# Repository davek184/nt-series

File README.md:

Changes from original nt-980
* Bottom row alternate layouts
* Stepped caps lock support
* Rotated numpad plus and enter keys
* Added alternate LED location under numlock key
* Added reset pin next to the right spacebar stab (to go into bootloader mode)
* Added second JST connector (JST 2.0 5 pin)
* Labeling on front and back (trying something)

It does work with the stock plate but only for the original layout.  Other layouts would require modding the plate or getting a new one.

NOTE: 
* **The JST connector uses a different PIN arrangement then the original Leopold daughter/middle board pay attention to the cable used if going for this connection method!**
* I didn't update the Schematic for the changes I made because I have no idea on how to do that and everytime I tried it caused more problems

Layouts supported

PCB

Actual photos here: https://imgur.com/a/Q7dKFkK

Use at your own risk.

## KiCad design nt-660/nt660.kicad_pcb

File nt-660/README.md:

# nt-660 PCB

Forked from Evyd13 with changes listed below with the goal to fit in the Norbauer heavy-6 case.  Thought none of the changes made will affect fitting in a standard fc660m usb-mini case.

(Do not forget the daughterboard in the subdirectory)

# Changes
- Added JST Connector for USB
- Added JST connector for RGB
- Added MegaMan logo
- Removed ISO enter (can be added back if you copy the footprint from evyd13's version and check the traces)

# Note: 
DO NOT populate the mini-usb connector if planning to use in Norbauer heavy-6 case!

# Render

More Photos in heavy-6: https://imgur.com/a/MOReMm4

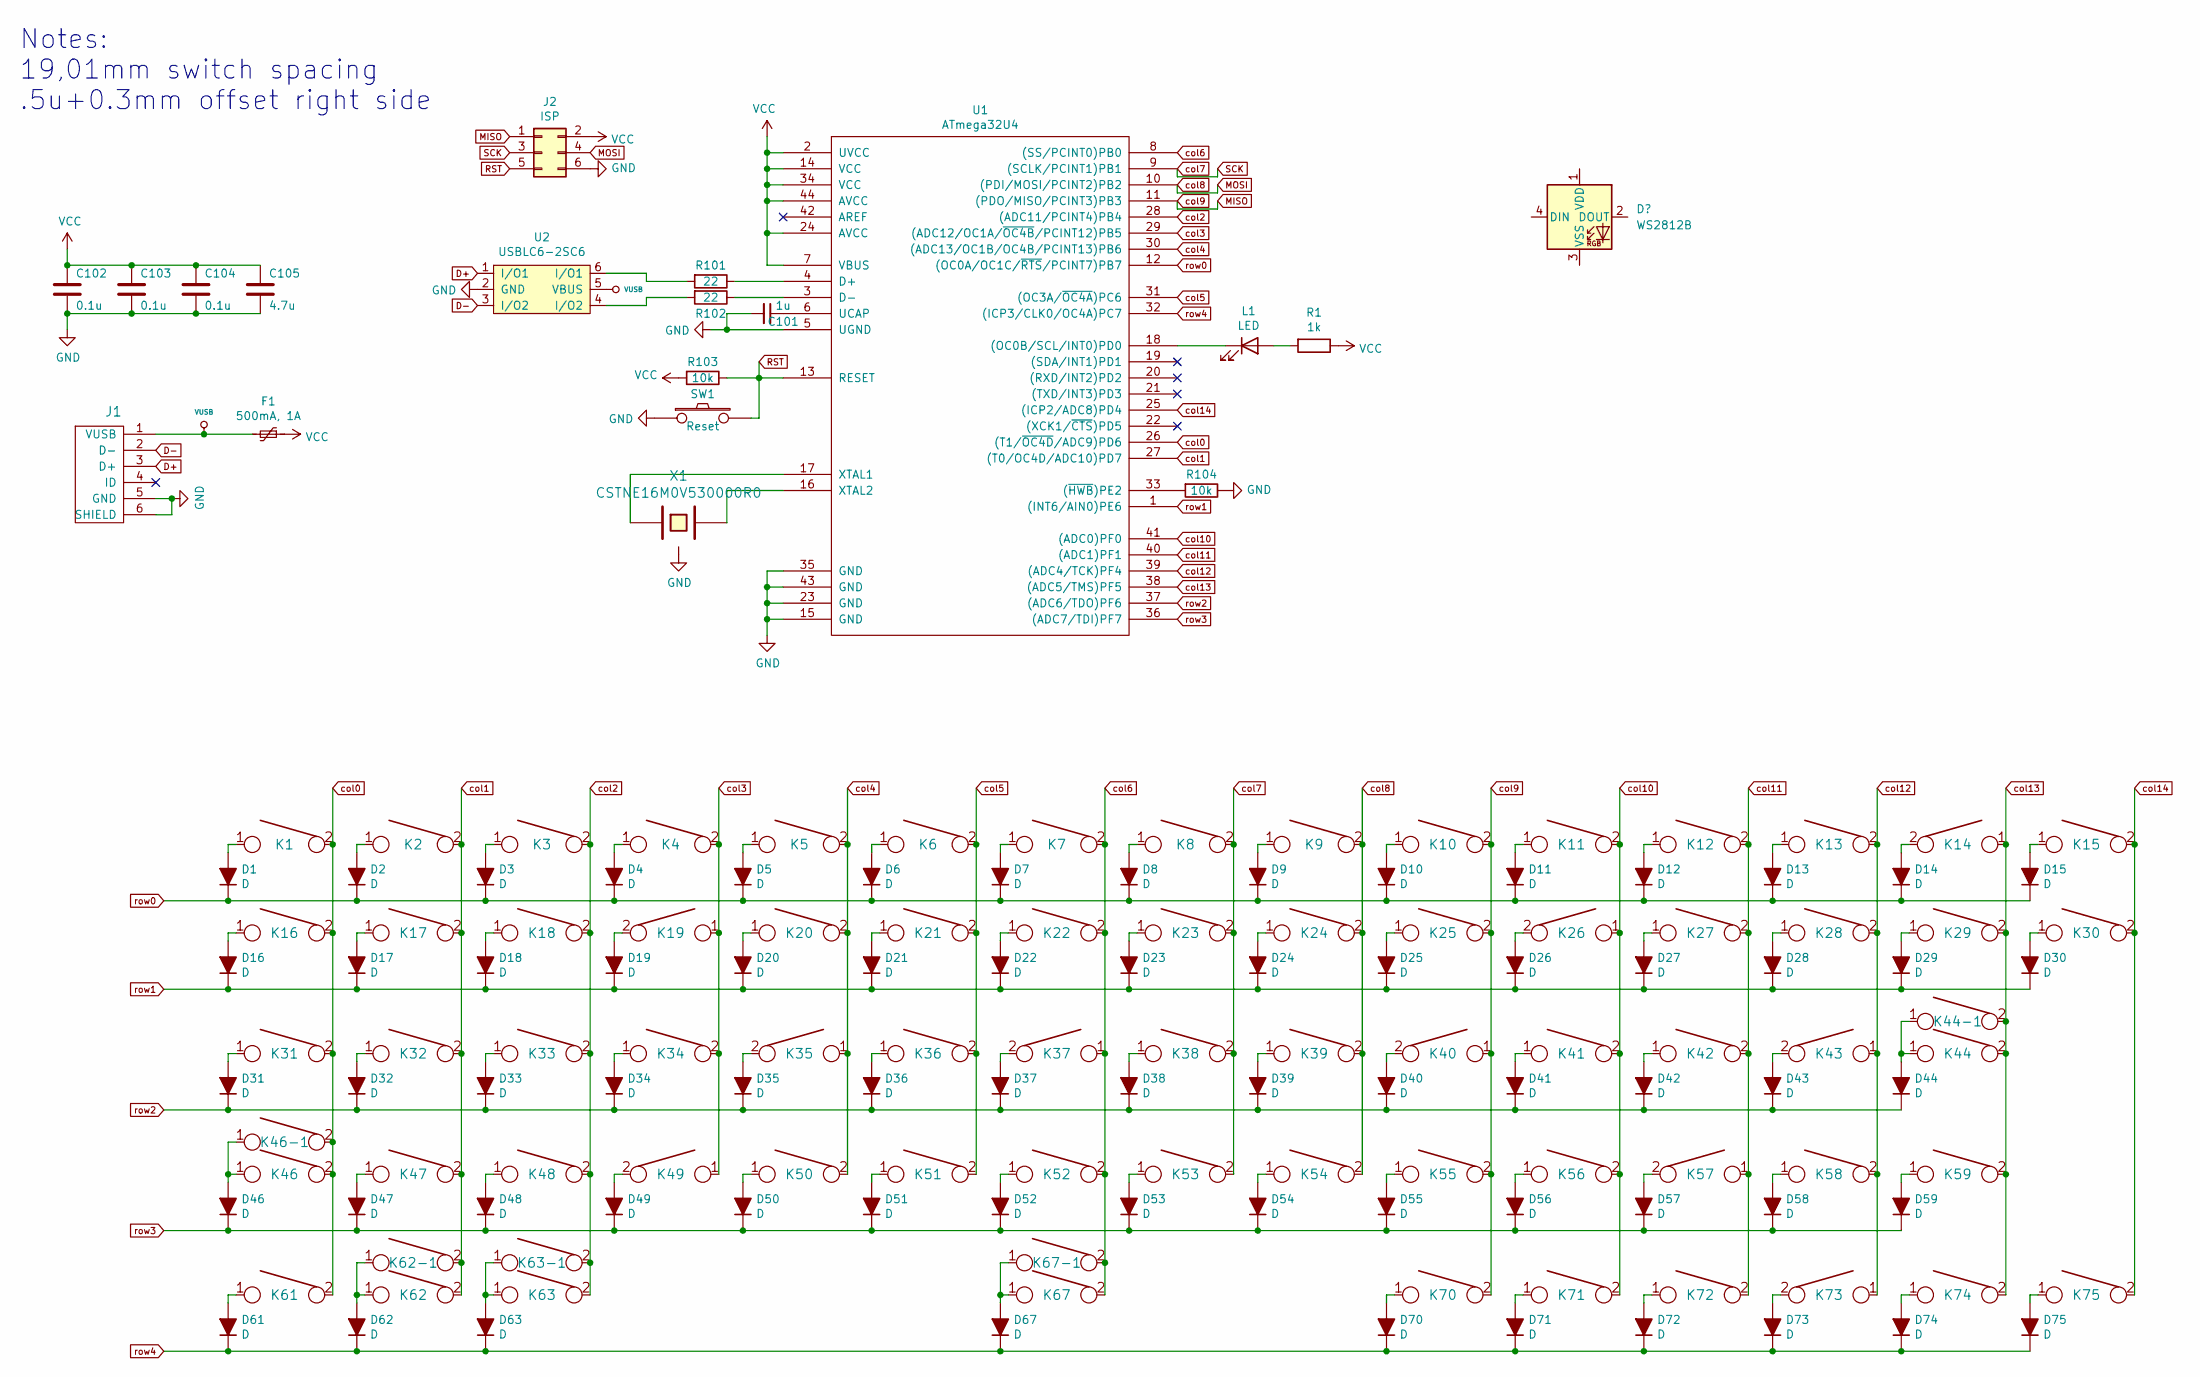
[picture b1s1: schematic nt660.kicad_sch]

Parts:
C101: 1u; C_0805
C102, C103, C104: 0.1u; C_0805
C105: 4.7u; C_0805
D1, D2, D3, D4, D5, D6, D7, D8, D9, D10, D11, D12, D13, D14, D15, D16, D17, D18, D19, D20, D21, D22, D23, D24, D25, D26, D27, D28, D29, D30, D31, D32, D33, D34, D35, D36, D37, D38, D39, D40, D41, D42, D43, D44, D46, D47, D48, D49, D50, D51, D52, D53, D54, D55, D56, D57, D58, D59, D61, D62, D63, D67, D70, D71, D72, D73, D74, D75: D; D_0805
F1: 500mA, 1A; R_0805
J1: USB_mini_micro_B; U-M-M5DD-W-1
J2: ISP; isp_standard
K1, K2, K3, K4, K5, K6, K7, K8, K9, K10, K11, K12, K13, K15, K17, K18, K19, K20, K21, K22, K23, K24, K25, K26, K27, K28, K30, K32, K33, K34, K35, K36, K37, K38, K39, K40, K41, K42, K43, K47, K48, K49, K50, K51, K52, K53, K54, K55, K56, K57, K59, K62, K73, K74, K75: KEYSW; CHERRY_PLATE_100H
K14: KEYSW; CHERRY_PCB_200H
K16, K29: KEYSW; CHERRY_PLATE_150H
K31: KEYSW; CHERRY_PLATE_175H
K44, K46, K58: KEYSW; CHERRY_PCB_225H
K44-1: KEYSW; CHERRY_PCB_200H_V
K46-1, K61, K62-1, K63, K63-1, K70, K71, K72: KEYSW; CHERRY_PLATE_125H
K67: KEYSW; CHERRY_PCB_625H_F
K67-1: KEYSW; CHERRY_PCB_600C_H_F
L1: LED; CHERRY_MX_LED
R1: 1k; R_0805
R101, R102: 22; R_0805
R103, R104: 10k; R_0805
SW1: Reset; SW_SPST_TL3342
U1: ATmega32U4; ATMEGA32U4
U2: USBLC6-2SC6
X1: CSTNE16M0V530000R0; Resonator_SMD_muRata_CSTNExxV-3Pin-p1.2

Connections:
D+: J1.3 (D+), U2.1 (I/O1); also elsewhere on the board
D-: J1.2 (D-), U2.3 (I/O2); also elsewhere on the board
GND: C101.2, C102.2, C103.2, C104.2, C105.2, J1.5 (GND), J1.6 (SHIELD), J2.6, R104.1, SW1.1, U1.5 (UGND), U1.15 (GND), U1.23 (GND), U1.35 (GND), U1.43 (GND), U2.2 (GND), X1.3; also elsewhere on the board
MISO: J2.1, K10.2, K25.2, K40.1, K55.2, K70.2, U1.11 ((PDO/MISO/PCINT3)PB3)
MOSI: J2.4, K9.2, K24.2, K39.2, K54.2, U1.10 ((PDI/MOSI/PCINT2)PB2)
unnamed: C101.1, U1.6 (UCAP)
unnamed: D1.2 (A), K1.1
unnamed: D2.2 (A), K2.1
unnamed: D3.2 (A), K3.1
unnamed: D4.2 (A), K4.1
unnamed: D5.2 (A), K5.1
unnamed: D6.2 (A), K6.1
unnamed: D7.2 (A), K7.1
unnamed: D8.2 (A), K8.1
unnamed: D9.2 (A), K9.1
unnamed: D10.2 (A), K10.1
unnamed: D11.2 (A), K11.1
unnamed: D12.2 (A), K12.1
unnamed: D13.2 (A), K13.1
unnamed: D14.2 (A), K14.2
unnamed: D15.2 (A), K15.1
unnamed: D16.2 (A), K16.1
unnamed: D17.2 (A), K17.1
unnamed: D18.2 (A), K18.1
unnamed: D19.2 (A), K19.2
unnamed: D20.2 (A), K20.1
unnamed: D21.2 (A), K21.1
unnamed: D22.2 (A), K22.1
unnamed: D23.2 (A), K23.1
unnamed: D24.2 (A), K24.1
unnamed: D25.2 (A), K25.1
unnamed: D26.2 (A), K26.2
unnamed: D27.2 (A), K27.1
unnamed: D28.2 (A), K28.1
unnamed: D29.2 (A), K29.1
unnamed: D30.2 (A), K30.1
unnamed 36: D31.2 (A), K31.1; also elsewhere on the board
unnamed: D32.2 (A), K32.1
unnamed: D33.2 (A), K33.1
unnamed: D34.2 (A), K34.1
unnamed: D35.2 (A), K35.2
unnamed: D36.2 (A), K36.1
unnamed: D37.2 (A), K37.2
unnamed: D38.2 (A), K38.1
unnamed: D39.2 (A), K39.1
unnamed: D40.2 (A), K40.2
unnamed: D41.2 (A), K41.1
unnamed: D42.2 (A), K42.1
unnamed: D43.2 (A), K43.2
unnamed: D44.2 (A), K44.1, K44-1.1
unnamed: D46.2 (A), K46.1, K46-1.1
unnamed: D47.2 (A), K47.1
unnamed: D48.2 (A), K48.1
unnamed: D49.2 (A), K49.2
unnamed: D50.2 (A), K50.1
unnamed: D51.2 (A), K51.1
unnamed: D52.2 (A), K52.1
unnamed: D53.2 (A), K53.1
unnamed: D54.2 (A), K54.1
unnamed: D55.2 (A), K55.1
unnamed: D56.2 (A), K56.1
unnamed: D57.2 (A), K57.2
unnamed: D58.2 (A), K58.1
unnamed: D59.2 (A), K59.1
unnamed: D61.2 (A), K61.1
unnamed: D62.2 (A), K62.1, K62-1.1
unnamed: D63.2 (A), K63.1, K63-1.1
unnamed: D67.2 (A), K67.1, K67-1.1
unnamed: D70.2 (A), K70.1
unnamed: D71.2 (A), K71.1
unnamed: D72.2 (A), K72.1
unnamed: D73.2 (A), K73.2
unnamed: D74.2 (A), K74.1
unnamed: D75.2 (A), K75.1
unnamed 74: L1.1 (K), U1.18 ((OC0B/SCL/INT0)PD0); also elsewhere on the board
unnamed 75: L1.2 (A), R1.2; also elsewhere on the board
unnamed: R101.1, U1.4 (D+)
unnamed: R101.2, U2.6 (I/O1)
unnamed: R102.1, U1.3 (D-)
unnamed: R102.2, U2.4 (I/O2)
unnamed: R104.2, U1.33 ((~HWB~)PE2)
unnamed: U1.16 (XTAL2), X1.2
unnamed: U1.17 (XTAL1), X1.1
RST: J2.5, R103.1, SW1.2, U1.13 (RESET)
SCK: J2.3, K8.2, K23.2, K38.2, K53.2, U1.9 ((SCLK/PCINT1)PB1)
VCC: C102.1, C103.1, C104.1, C105.1, F1.1, J2.2, R1.1, R103.2, U1.2 (UVCC), U1.7 (VBUS), U1.14 (VCC), U1.24 (AVCC), U1.34 (VCC), U1.44 (AVCC)
VUSB: F1.2, J1.1 (VUSB), U2.5 (VBUS); also elsewhere on the board
col0: K1.2, K16.2, K31.2, K46.2, K46-1.2, K61.2, U1.26 ((T1/~OC4D~/ADC9)PD6); also elsewhere on the board
col1: K2.2, K17.2, K32.2, K47.2, K62.2, K62-1.2, U1.27 ((T0/OC4D/ADC10)PD7)
col2: K3.2, K18.2, K33.2, K48.2, K63.2, K63-1.2, U1.28 ((ADC11/PCINT4)PB4)
col3: K4.2, K19.1, K34.2, K49.1, U1.29 ((ADC12/OC1A/~OC4B~/PCINT12)PB5)
col4: K5.2, K20.2, K35.1, K50.2, U1.30 ((ADC13/OC1B/OC4B/PCINT13)PB6)
col5: K6.2, K21.2, K36.2, K51.2, U1.31 ((OC3A/~OC4A~)PC6)
col6: K7.2, K22.2, K37.1, K52.2, K67.2, K67-1.2, U1.8 ((SS/PCINT0)PB0)
col10: K11.2, K26.1, K41.2, K56.2, K71.2, U1.41 ((ADC0)PF0)
col11: K12.2, K27.2, K42.2, K57.1, K72.2, U1.40 ((ADC1)PF1)
col12: K13.2, K28.2, K43.1, K58.2, K73.1, U1.39 ((ADC4/TCK)PF4)
col13: K14.1, K29.2, K44.2, K44-1.2, K59.2, K74.2, U1.38 ((ADC5/TMS)PF5)
col14: K15.2, K30.2, K75.2, U1.22 ((XCK1/~CTS~)PD5), U1.25 ((ICP2/ADC8)PD4); also elsewhere on the board
row0: D1.1 (K), D2.1 (K), D3.1 (K), D4.1 (K), D5.1 (K), D6.1 (K), D7.1 (K), D8.1 (K), D9.1 (K), D10.1 (K), D11.1 (K), D12.1 (K), D13.1 (K), D14.1 (K), D15.1 (K), U1.12 ((OC0A/OC1C/~RTS~/PCINT7)PB7)
row1: D16.1 (K), D17.1 (K), D18.1 (K), D19.1 (K), D20.1 (K), D21.1 (K), D22.1 (K), D23.1 (K), D24.1 (K), D25.1 (K), D26.1 (K), D27.1 (K), D28.1 (K), D29.1 (K), D30.1 (K), U1.1 ((INT6/AIN0)PE6)
row2: D31.1 (K), D32.1 (K), D33.1 (K), D34.1 (K), D35.1 (K), D36.1 (K), D37.1 (K), D38.1 (K), D39.1 (K), D40.1 (K), D41.1 (K), D42.1 (K), D43.1 (K), D44.1 (K), U1.37 ((ADC6/TDO)PF6)
row3: D46.1 (K), D47.1 (K), D48.1 (K), D49.1 (K), D50.1 (K), D51.1 (K), D52.1 (K), D53.1 (K), D54.1 (K), D55.1 (K), D56.1 (K), D57.1 (K), D58.1 (K), D59.1 (K), U1.36 ((ADC7/TDI)PF7)
row4: D61.1 (K), D62.1 (K), D63.1 (K), D67.1 (K), D70.1 (K), D71.1 (K), D72.1 (K), D73.1 (K), D74.1 (K), D75.1 (K), U1.32 ((ICP3/CLK0/OC4A)PC7)

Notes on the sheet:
Notes: 19,01mm switch spacing .5u+0.3mm offset right side

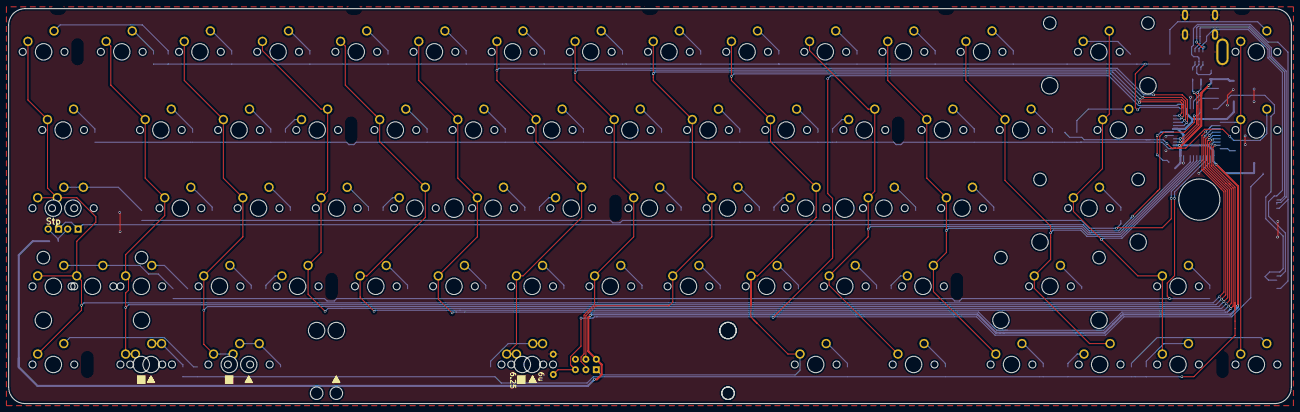
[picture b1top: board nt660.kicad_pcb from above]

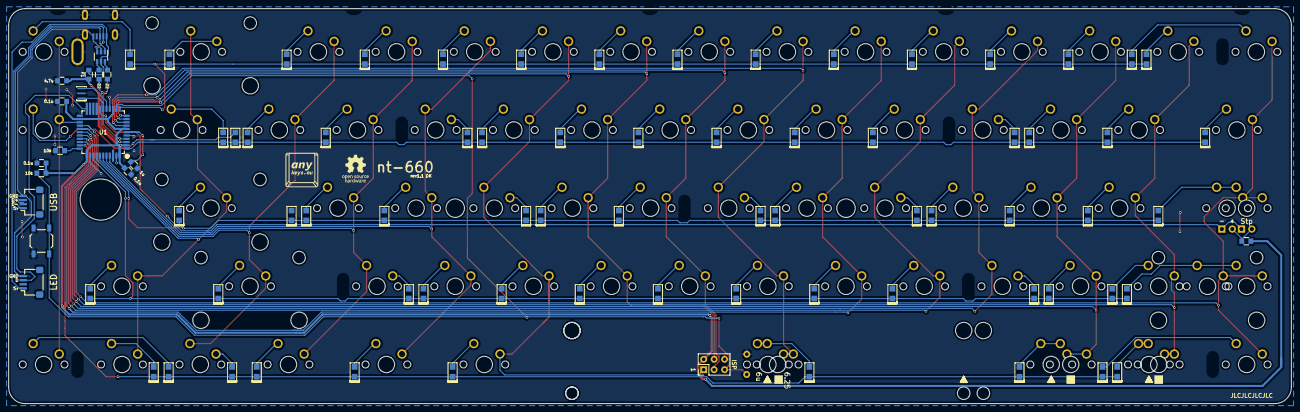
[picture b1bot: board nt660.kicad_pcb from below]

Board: 2 copper layers, 312.0 x 96.1 mm, 161 parts (87 on the bottom side), 103 nets.

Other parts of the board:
J3, J4: ai03_ud; JST_SH_SM04B-SRSS-TB_1x04-1MP_P1.00mm_Horizontal
K31-1: KEYSW; CHERRY_PLATE_175H
L1#2: LED; CHERRY_MX_LED

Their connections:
D+: J3.3; also elsewhere on the board
D-: J3.2; also elsewhere on the board
GND: J3.4, J4.4; also elsewhere on the board
unnamed 36: K31-1.1; also elsewhere on the board
unnamed 74: L1#2.1 (K); also elsewhere on the board
unnamed 75: L1#2.2 (A); also elsewhere on the board
VUSB: J3.1, J4.1; also elsewhere on the board
col0: K31-1.2; also elsewhere on the board
col14: J4.3; also elsewhere on the board

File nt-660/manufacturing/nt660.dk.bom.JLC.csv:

Comment,Designator,Footprint,LCSC
0.1u,"C102,C103,C104",805,C49678
4.7u,C105,805,C1779
1u,C101,805,C28323
Diode,"D2,D3,D4,D5,D6,D7,D8,D9,D10,D11,D12,D13,D14,D15,D16,D17,D18,D19,D20,D21,D22,D23,D24,D25,D26,D27,D28,D29,D31,D32,D33,D34,D35,D36,D37,D38,D39,D40,D41,D42,D43,D44,D46,D47,D48,D49,D50,D51,D52,D53,D54,D55,D56,D57,D58,D59,D61,D62,D63,D67,D70,D71,D72,D73,D74,D75,D1,D30",805,C81598
"Fuse 500mA, 1A",F1,805,C261942
10k,"R103,R104",805,C17414
1k,R1,805,C17513
22,"R101,R102",805,C17561
ATmega32U4,U1,QFP-44,C44854
Resonator_16MHz_SMD,X1,SMD,C341521
ESD,U2,SOT-23-6L,C7519
ResetSwitch:SW_SPST_TL3342,SW1,SMD,C92584
Connector,"J3,J4",SMD,C160404

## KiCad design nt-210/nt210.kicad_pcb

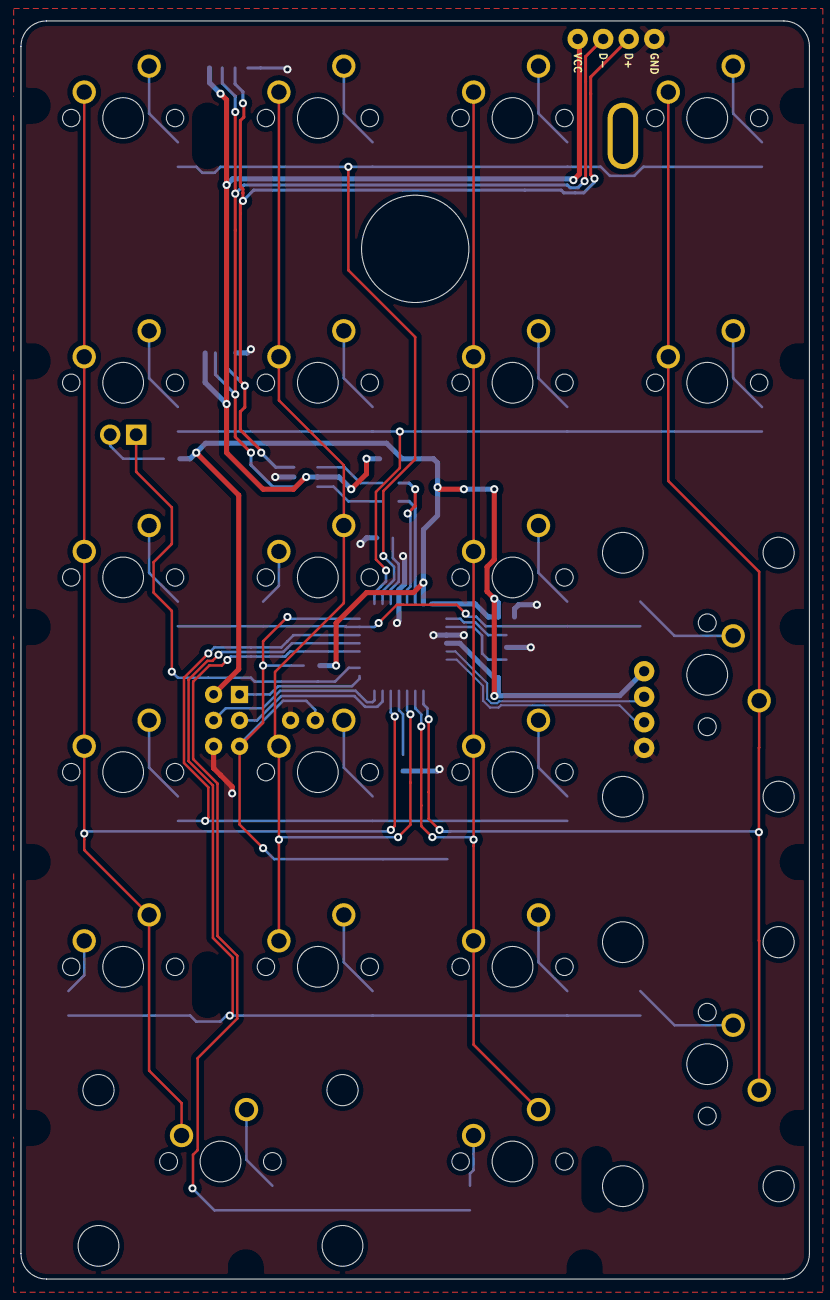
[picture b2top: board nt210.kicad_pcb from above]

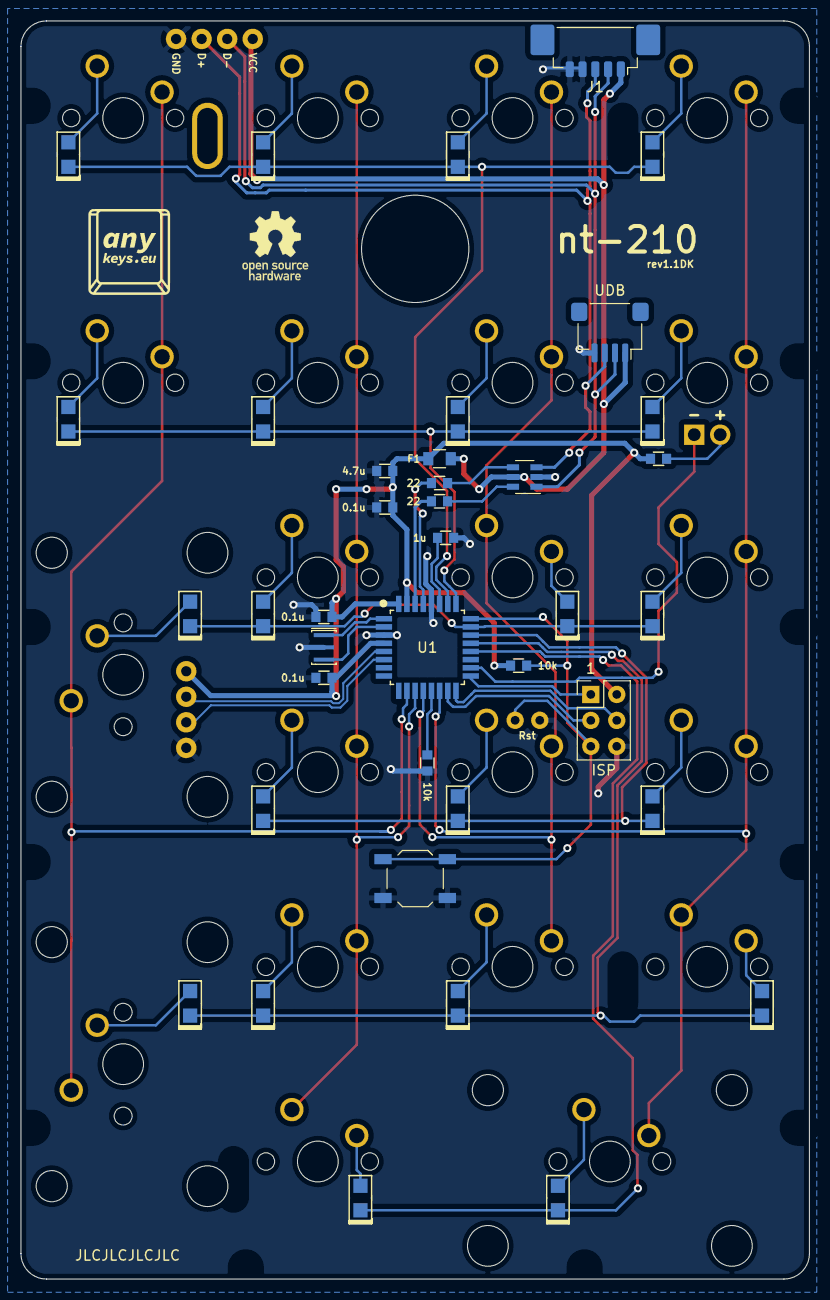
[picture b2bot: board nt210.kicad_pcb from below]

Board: 2 copper layers, 77.2 x 123.1 mm, 62 parts (39 on the bottom side), 50 nets.

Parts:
C1, C2, C3: 0.1u; C_0603
C4: 4.7u; C_0603
C5: 1u; C_0603
D1, D2, D3, D4, D5, D6, D7, D8, D9, D10, D11, D12, D13, D14, D15, D17, D18, D19, D20, D21, D23: D; D_0805
F1: Fuse; F_0805
J1: 53398-0571; Molex-PicoBlade-533980571
J2: ISP; isp_standard
J3: UDB; JST_SH_SM04B-SRSS-TB_1x04-1MP_P1.00mm_Horizontal
J4: Solder header; solder_header
K1, K2, K3, K4, K5, K6, K7, K8, K9, K10, K11, K13, K14, K15, K17, K18, K19, K23: KEYSW; CHERRY_PLATE_100H
K20, K20#2, K21: KEYSW; Mx-2.00U
L1: LED; CHERRY_MX_LED_neo
R1, R2: 22; R_0603
R3, R4: 10k; R_0603
R5: 1k; R_0603
SW1: Reset; SW_SPST_TL3342
U1: ATMEGA32U2
U2: USBLC6-2SC6
X1: 16mhz; Resonator_SMD_muRata_CSTNExxV-3Pin-p1.2

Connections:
D+: J1.3, J3.3, J4.3, U1.5 (PC2), U2.3 (I/O2)
D-: J1.2, J3.2, J4.2, U1.6 (PD0), U2.1 (I/O1)
GND: C1.2, C2.2, C3.2, C4.2, C5.2, J1.4, J1.5, J2.6, J3.4, J4.4, R3.1, SW1.1, U1.3 (GND), U1.28 (UGND), U2.2 (GND), X1.3
MISO: J2.1, U1.17 (PB3)
MOSI: J2.4, U1.16 (PB2)
unnamed: C5.1, U1.27 (UCap)
unnamed: D1.2 (A), K1.1
unnamed: D2.2 (A), K2.1
unnamed: D3.2 (A), K3.1
unnamed: D4.2 (A), K4.1
unnamed: D5.2 (A), K5.1
unnamed: D6.2 (A), K6.1
unnamed: D7.2 (A), K7.1
unnamed: D8.2 (A), K8.1
unnamed: D9.2 (A), K9.1
unnamed: D10.2 (A), K10.2
unnamed: D11.2 (A), K11.1
unnamed: D12.2 (A), K20.2
unnamed: D13.2 (A), K13.1
unnamed: D14.2 (A), K14.1
unnamed: D15.2 (A), K15.1
unnamed: D17.2 (A), K17.2
unnamed: D18.2 (A), K18.1
unnamed: D19.2 (A), K19.1
unnamed: D20.2 (A), K20#2.2
unnamed: D21.2 (A), K21.1
unnamed: D23.2 (A), K23.2
unnamed: L1.1 (K), U1.18 (PB4)
unnamed: L1.2 (A), R5.2
unnamed: R1.1, U1.30 (D-)
unnamed: R1.2, U2.6 (I/O1)
unnamed: R2.1, U1.29 (D+)
unnamed: R2.2, U2.4 (I/O2)
unnamed: R3.2, U1.13 (PD7/~HWB)
unnamed: U1.1 (XTAL1), X1.1
unnamed: U1.2 (XTAL2), X1.2
RST: J2.5, R4.1, SW1.2, U1.24 (~RESET)
SCK: J2.3, U1.15 (PB1)
VCC: C1.1, C2.1, C3.1, C4.1, F1.1, J2.2, R4.2, R5.1, U1.4 (VCC), U1.31 (UVCC), U1.32 (AVCC)
VUSB: F1.2, J1.1, J3.1, J4.1, U2.5 (VBUS)
col0: K1.2, K5.2, K9.2, K13.2, K17.1, K21.2, U1.14 (PB0)
col1: K2.2, K6.2, K10.1, K14.2, K18.2, U1.12 (PD6)
col2: K3.2, K7.2, K11.2, K15.2, K19.2, K23.1, U1.11 (PD5)
col3: K4.2, K8.2, K20.1, K20#2.1, U1.10 (PD4)
row0: D1.1 (K), D2.1 (K), D3.1 (K), D4.1 (K), U1.26 (PC4)
row1: D5.1 (K), D6.1 (K), D7.1 (K), D8.1 (K), U1.25 (PC5)
row2: D9.1 (K), D10.1 (K), D11.1 (K), D12.1 (K), U1.23 (PC6)
row3: D13.1 (K), D14.1 (K), D15.1 (K), U1.22 (PC7)
row4: D17.1 (K), D18.1 (K), D19.1 (K), D20.1 (K), U1.21 (PB7)
row5: D21.1 (K), D23.1 (K), U1.20 (PB6)

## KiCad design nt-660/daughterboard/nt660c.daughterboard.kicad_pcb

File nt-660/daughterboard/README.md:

# Daughterboard

USB-C daughterboard for Norbauer's Heavy-6 case. 

# Manufacturing:
 - Files in Manufacturing folder are setup for JLCPCB
 - Note: Choose Specify a location under Remove order number

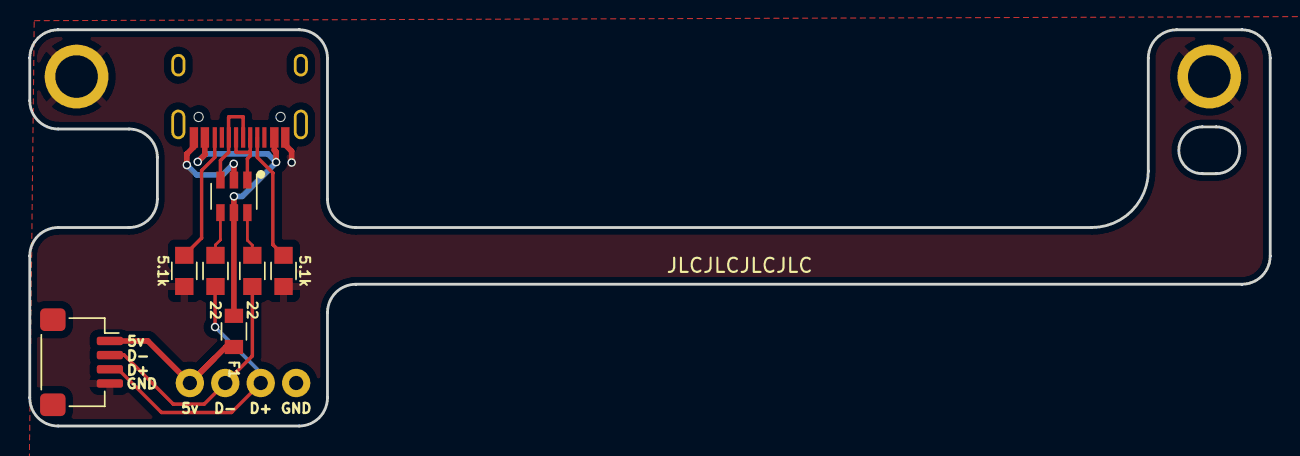
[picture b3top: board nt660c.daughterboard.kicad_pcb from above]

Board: 2 copper layers, 87.5 x 27.9 mm, 11 parts (0 on the bottom side), 11 nets.

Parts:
F1: Polyfuse_Small; F_0805
J1: HRO-TYPE-C-31-M-12
J2: ai03_ud; JST_SH_SM04B-SRSS-TB_1x04-1MP_P1.00mm_Horizontal
J4: Solder header; solder_header
R1, R2: 22; R_0805
R5, R6: 5.1k; R_0805
S1, S2: SCREW; screw
U2: USBLC6-2SC6

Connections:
D+: R1.1, U2.4 (I/O2)
D-: R2.1, U2.6 (I/O1)
GND: J1.1 (GND), J1.12 (GND), J2.4, R5.2, R6.2, S1.1, S2.1, U2.2 (GND)
unnamed: J1.4 (CC1), R5.1
unnamed: J1.5 (DN2), J1.7 (DN1), U2.1 (I/O1)
unnamed: J1.6 (DP1), J1.8 (DP2), U2.3 (I/O2)
unnamed: J1.10 (CC2), R6.1
unnamed: J2.3, J4.3, R1.2
unnamed: J2.2, J4.2, R2.2
VBUS: F1.2, J1.2 (VBUS), J1.11 (VBUS), U2.5 (VBUS)
VCC: F1.1, J2.1, J4.1

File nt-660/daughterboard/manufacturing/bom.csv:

Designator,Footprint,Quantity,Value,LCSC Part #
F1,F_0805,1,Polyfuse_Small,C261942
R5,R_0805,1,5.1k,C212411
J2,JST_SH_SM04B-SRSS-TB_1x04-1MP_P1.00mm_Horizontal,1,ai03_ud,C160404
J1,HRO-TYPE-C-31-M-12,1,HRO-TYPE-C-31-M-12,C165948
R1,R_0805,1,22,C325772
R6,R_0805,1,5.1k,C212411
U2,USBLC6-2SC6,1,USBLC6-2SC6,C7519
R2,R_0805,1,22,C325772

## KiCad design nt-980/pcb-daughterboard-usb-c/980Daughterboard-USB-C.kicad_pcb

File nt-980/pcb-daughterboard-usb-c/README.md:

# Moved to seperate repo:

https://github.com/davek184/980_Usb_C_Daughterboard

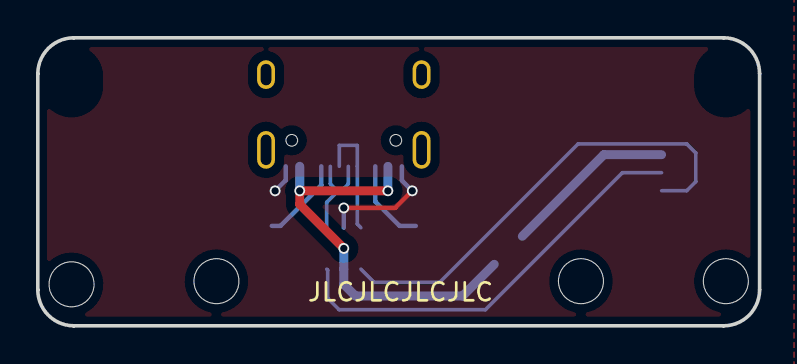
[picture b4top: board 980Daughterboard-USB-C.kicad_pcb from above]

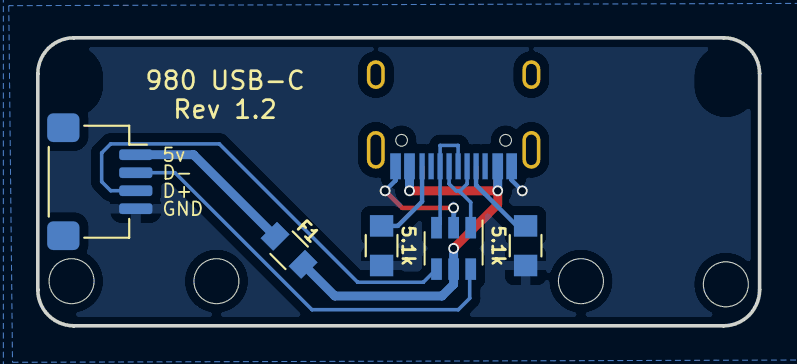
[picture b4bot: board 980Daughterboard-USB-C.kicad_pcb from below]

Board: 2 copper layers, 40.1 x 16.0 mm, 6 parts (6 on the bottom side), 8 nets.

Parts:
F1: Polyfuse_Small; F_0805
J1: TYPE-C-31-M-12; HRO-TYPE-C-31-M-12
J2: ai03_ud; JST_SH_SM04B-SRSS-TB_1x04-1MP_P1.00mm_Horizontal
R1, R2: 5.1k; R_0805
U1: USBLC6-2SC6

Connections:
D+: J2.3, U1.4 (I/O2)
D-: J2.2, U1.6 (I/O1)
GND: J1.1 (GND), J1.12 (GND), J2.4, R1.2, R2.2, U1.2 (GND)
unnamed: J1.4 (CC1), R1.1
unnamed: J1.5 (DN2), J1.7 (DN1), U1.1 (I/O1)
unnamed: J1.6 (DP1), J1.8 (DP2), U1.3 (I/O2)
unnamed: J1.10 (CC2), R2.1
VBUS: F1.1, F1.2, J1.2 (VBUS), J1.11 (VBUS), J2.1, U1.5 (VBUS)

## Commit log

2021-09-19 Create production-JLCPCB
2021-12-24 Create read
2021-12-24 Rename read to README.md
2022-01-04 USB-Mini Daughterboard
2022-01-16 Add files via upload
    From Tinster4x4 adapter for Keebio USB-C breakout board to stock case
2022-04-15 Add files via upload
    Interactive BOM for version 1.2
2022-04-22 Revision 1.0
2022-04-22 Revision 1.2
2022-05-02 Adding Rev 1.0 backup
2022-08-31 Add Daughterboard
2022-08-31 add JLCPCB manufacturing files
2022-08-31 fixed gerber file
2022-09-05 Create KLE
2022-11-09 Production files version 1.3
    Added JST/QWIIC connectors to production assembly bom/pos files
2022-11-09 Updated iBOM
2022-11-09 Design fixed designators for QWIIC connectors
2023-02-12 nt-210dk
    Deviated from Evy's removed extra keys. Added reset pins and breakout mcu pins
